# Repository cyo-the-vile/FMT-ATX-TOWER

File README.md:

# FMT-ATX-TOWER
A modification to revive a dead FM Towns tower model

[https://townsworld.com/2021/05/08/fm-towns-tower-power-supply-assembly-guide/](https://web.archive.org/web/20230320093739/https://townsworld.com/2021/05/08/fm-towns-tower-power-supply-assembly-guide/)

Uses an Arduino PRO Micro to control power on and TownsOS power off functions just like the original power supply.

Some of the mounting holes might not be exact.  At a later time, I need to measure the holes again but I don't own an original PCB anymore.  It is safe to file and cut around the screw points on the outer edges.

To order a PCB, go to factory output folder and select the RAR file.

Works on the following models:

1F
2F
SF
SH
1H
2H
10F
20F
40H
80H
SF2
SH2
CX10
CX20
CX40
CX100

It WILL NOT WORK for the following models:

S1
S2
MODEL1
MODEL2

You will need the following parts:

1    PCN13-44S-2.54DS
1	 39-28-1243    or you can use 39-28-1203.    It is preferred to use 39-28-1243
1    Arduino Pro Micro and Micro USB cable.  You need to load the firmware for the Arduino Pro Micro
1    Some male 2.54mm pin headers.
1    Pico PSU rated at 90W or higher such as this one   https://www.mini-box.com/picoPSU-90     The prototype was tested with 160W but I have found 90W is fine.
		Pico PSU have been cloned and their performance might vary. I recommend using the authentic mini-box brand.
1    AC/DC Converter.  The board can physically fit the EPS-120-12 or the EPS-120S-12.  Basically, an ACDC Converter that outputs 12V in a 2x3 or 2x4 (those are inches) form factor is fine.

日本人にとって、機械翻訳です。 あなたが困難を持っている場合は、Twitterで私に連絡してください。@cyothevile

死んだFMタウンズタワーモデルを復活させるための修正

[https://townsworld.com/2021/05/08/fm-towns-tower-power-supply-assembly-guide/](https://web.archive.org/web/20230320093739/https://townsworld.com/2021/05/08/fm-towns-tower-power-supply-assembly-guide/)

Arduino PRO Microを使用して、元の電源と同様に電源オンとTownsOSの電源オフ機能を制御します。

取り付け穴の中には、正確でないものもあります。 後で、私は再び穴を測定する必要がありますが、私はもう元のPCBを所有していません。 外縁のネジ点の周りをヤスリで留めて切断しても安全です。

PCBを注文するには、工場出荷時の出力フォルダに移動し、RARファイルを選択します。

次のモデルで動作します。

1F
2F
SF
SH
1H
2H
10F
20F
40H
80H
SF2
SH2
CX10
CX20
CX40
CX100

次のモデルでは動作しません。

S1
S2 
モデル1 or Model 1
モデル2 or Model 2

次の部品が必要です。

次の部品が必要です。

1 PCN13-44S-2.54DS
1 39-28-1243 または 39-28-1203 を使用できます。   39-28-1243 を使用することをお勧めします。
1 ArduinoプロマイクロとマイクロUSBケーブル。 Arduinoプロマイクロのファームウェアをロードする必要があります
1 いくつかのオス2.54mmピンヘッダー。
1 Pico PSUは、このような90W以上で定格 https://www.mini-box.com/picoPSU-90 プロトタイプは160Wでテストされましたが、90Wは問題ありません。
		Pico PSUはクローン化されており、それらのパフォーマンスは異なる場合があります。私は本物のミニボックスブランドを使用することをお勧めします。
1 AC / DCコンバータ。 ボードはEPS-120-12またはEPS-120S-12に物理的にフィットすることができます。 基本的に、2x3または2x4(これらはインチ)のフォームファクタで12Vを出力するACDCコンバータは問題ありません。

******************************************************

Generation 1 Tower card 

 - Requires more testing.  Should be safe for testing.

Please follow precise instructions here:  [https://townsworld.com/2021/06/01/fm-towns-power-supply-generation-1/](https://web.archive.org/web/20230603034252/https://townsworld.com/2021/06/01/fm-towns-power-supply-generation-1/)

VMS-180C-12
VOF-180C-12
VMS-200C-12

These are the recommended ACDC converters to place on the card.  The Generation 1 Towers appear to use more power.  A 160W Pico is recommended until further testing is completed.

ジェネレーション1タワーカード

日本人の友達、困ったら連絡してください。 TWITTER@cyo.the.vile

- さらにテストが必要です。テストのために安全でなければなりません。

こちらの正確な指示に従ってください: [https://townsworld.com/2021/06/01/fm-towns-power-supply-generation-1/](https://web.archive.org/web/20230603034252/https://townsworld.com/2021/06/01/fm-towns-power-supply-generation-1/)

VMS-180C-12
VOF-180C-12
VMS-200C-12

これらは、カードに配置する推奨 ACDC コンバータです。第 1 世代のタワーは、より多くの電力を使用しているようです。 さらなるテストが完了するまでは、160W Pico をお勧めします。

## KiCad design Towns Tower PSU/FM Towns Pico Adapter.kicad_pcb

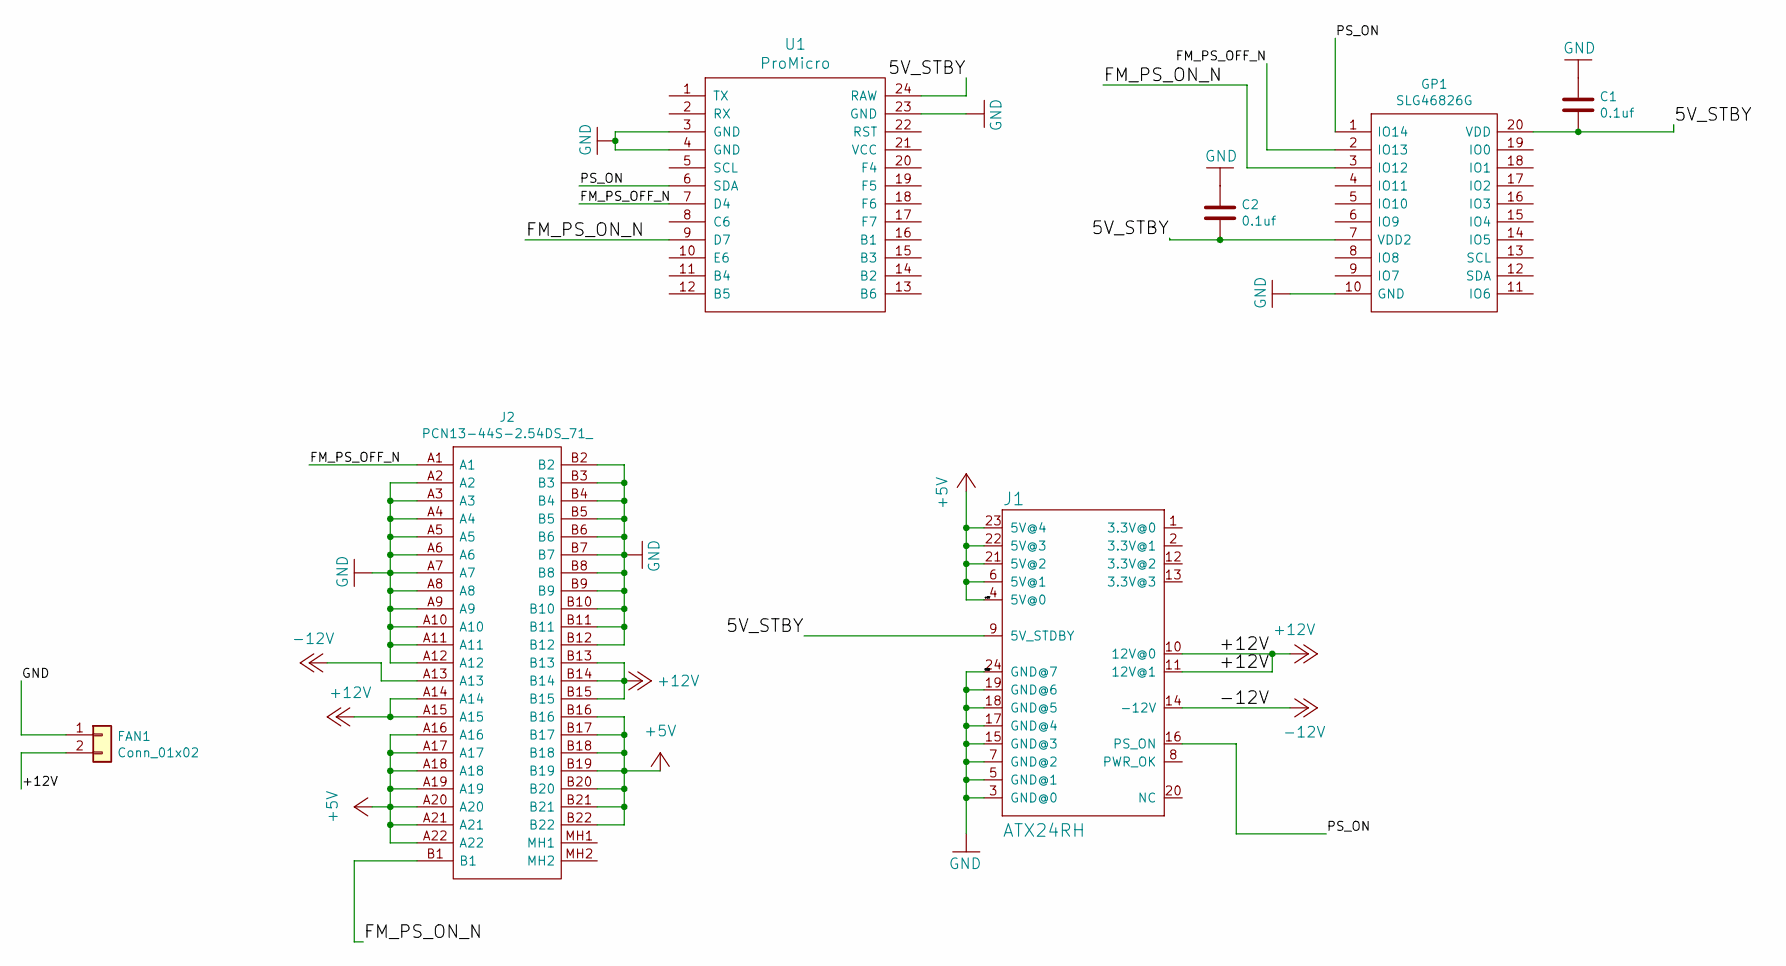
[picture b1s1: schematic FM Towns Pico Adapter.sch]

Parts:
C1, C2: 0.1uf; C_1206_3216Metric
FAN1: Conn_01x02; PinHeader_1x02_P2.54mm_Vertical
GP1: SLG46826G; SOP65P640X120-20N; Manufacturer_Part_Number SLG46826G; Mouser Part Number 724-SLG46826G
J1: ATX24RH; ATX24_RIGHT_ANGLE
J2: PCN13-44S-2.54DS_71_; PCN1344S254DS71; Manufacturer_Part_Number PCN13-44S-2.54DS(71); Mouser Part Number 798-PCN1344S254DS71
U1: ProMicro

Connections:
+5V: J1.4 (5V@0), J1.6 (5V@1), J1.21 (5V@2), J1.22 (5V@3), J1.23 (5V@4), J2.A16, J2.A17, J2.A18, J2.A19, J2.A20, J2.A21, J2.A22, J2.B16, J2.B17, J2.B18, J2.B19, J2.B20, J2.B21, J2.B22
+12V: FAN1.2, J1.10 (12V@0), J1.11 (12V@1), J2.A14, J2.A15, J2.B13, J2.B14, J2.B15
-12V: J1.14 (-12V), J2.A13
/5V_STBY: C1.2, C2.2, GP1.7 (VDD2), GP1.20 (VDD), J1.9 (5V_STDBY), U1.24 (RAW)
/FM_PS_OFF_N: GP1.2 (IO13), J2.A1, U1.7 (D4)
/FM_PS_ON_N: GP1.3 (IO12), J2.B1, U1.9 (D7)
/PS_ON: GP1.1 (IO14), J1.16 (PS_ON), U1.6 (SDA)
GND: C1.1, C2.1, FAN1.1, GP1.10 (GND), J1.3 (GND@0), J1.5 (GND@1), J1.7 (GND@2), J1.15 (GND@3), J1.17 (GND@4), J1.18 (GND@5), J1.19 (GND@6), J1.24 (GND@7), J2.A2, J2.A3, J2.A4, J2.A5, J2.A6, J2.A7, J2.A8, J2.A9, J2.A10, J2.A11, J2.A12, J2.B2, J2.B3, J2.B4, J2.B5, J2.B6, J2.B7, J2.B8, J2.B9, J2.B10, J2.B11, J2.B12, U1.3 (GND), U1.4 (GND), U1.23 (GND)

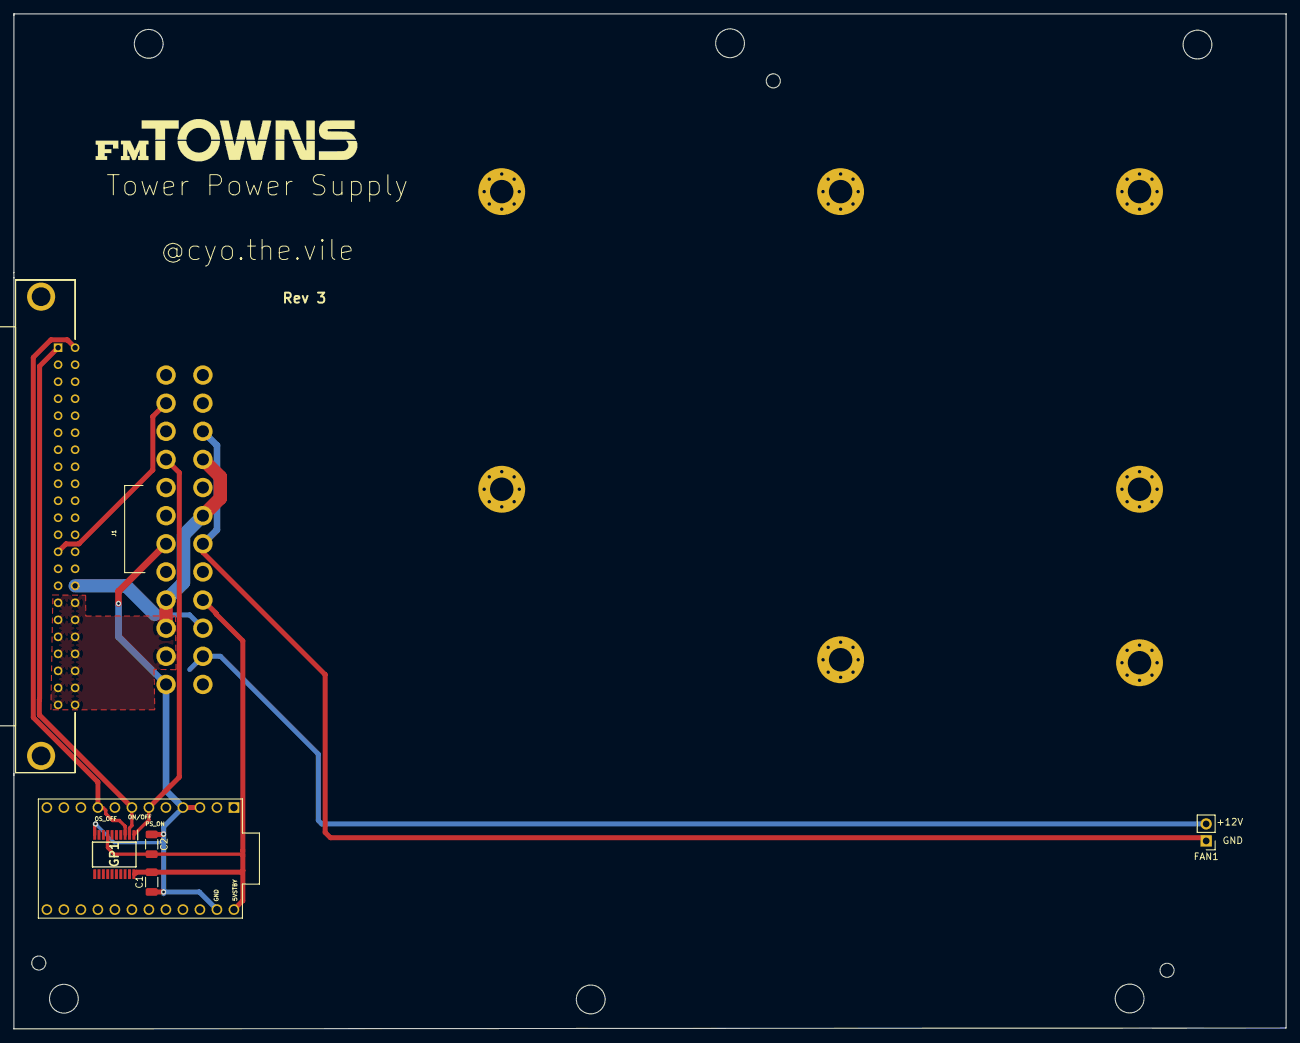
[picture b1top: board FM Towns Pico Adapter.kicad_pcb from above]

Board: 2 copper layers, 190.0 x 151.6 mm, 14 parts (0 on the bottom side), 8 nets.

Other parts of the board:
PAD1, PAD1#2, PAD1#3, PAD1#4, PAD2, PAD3, PAD4: MountingHole_3.5mm_Pad_Via

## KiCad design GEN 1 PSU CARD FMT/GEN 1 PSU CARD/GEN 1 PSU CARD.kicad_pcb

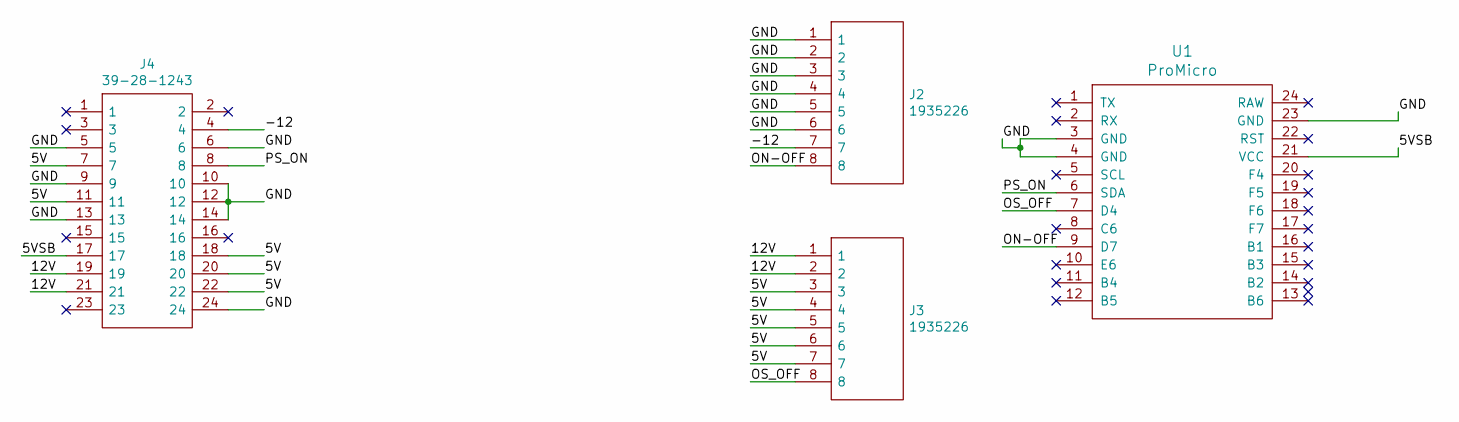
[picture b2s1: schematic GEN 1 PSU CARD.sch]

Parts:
J2, J3: 1935226; TerminalBlock_Phoenix_PT-1,5-8-3.5-H_1x08_P3.50mm_Horizontal; Manufacturer_Part_Number 1935226; Mouser Part Number 651-1935226
J4: 39-28-1243; SHDR24W125P550X420_2X12_5160X960X1310P; Manufacturer_Part_Number 39-28-1243; Mouser Part Number 538-39-28-1243
U1: ProMicro

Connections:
/5V: J3.3, J3.4, J3.5, J3.6, J3.7, J4.7, J4.11, J4.18, J4.20, J4.22
/5VSB: J4.17, U1.21 (VCC)
/12V: J3.1, J3.2, J4.19, J4.21
/-12: J2.7, J4.4
/GND: J2.1, J2.2, J2.3, J2.4, J2.5, J2.6, J4.5, J4.6, J4.9, J4.10, J4.12, J4.13, J4.14, J4.24, U1.3 (GND), U1.4 (GND), U1.23 (GND)
/ON-OFF: J2.8, U1.9 (D7)
/OS_OFF: J3.8, U1.7 (D4)
/PS_ON: J4.8, U1.6 (SDA)

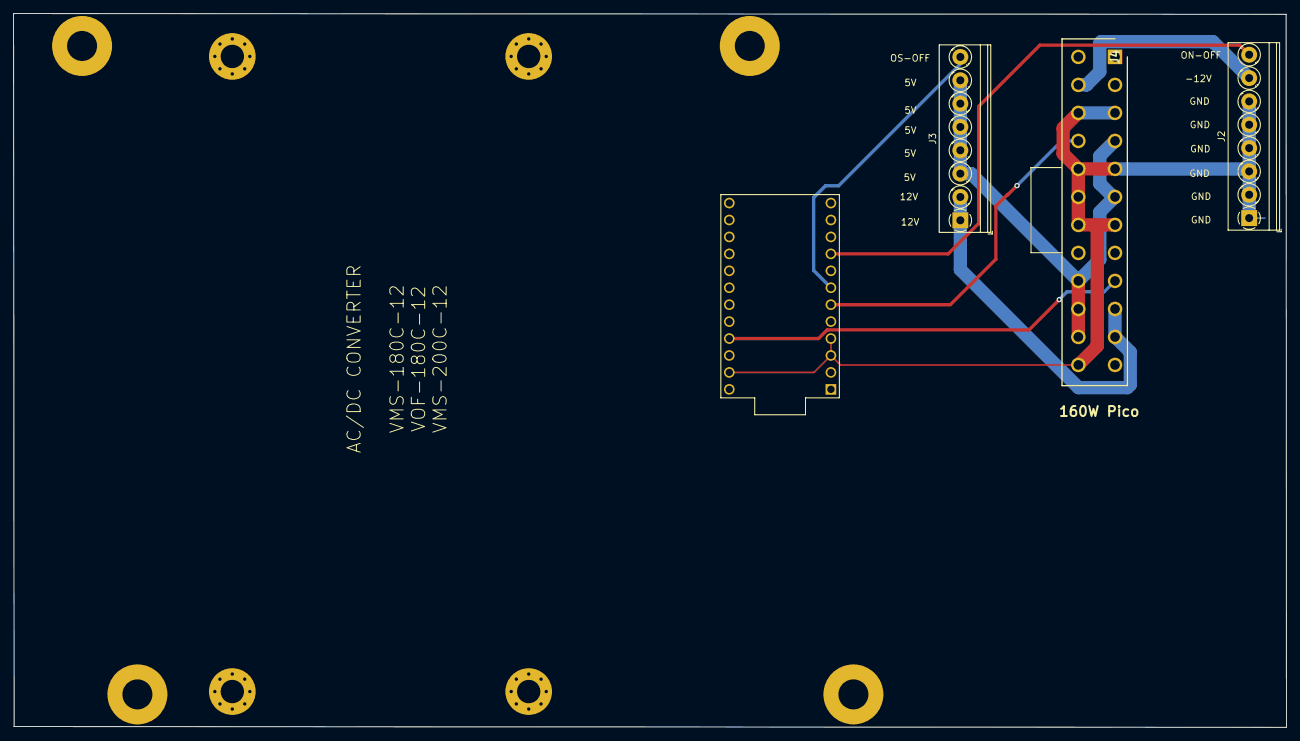
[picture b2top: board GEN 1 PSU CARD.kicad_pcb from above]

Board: 2 copper layers, 190.9 x 107.1 mm, 4 parts (0 on the bottom side), 8 nets.

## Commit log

2021-07-02 Update README.md
    Japanese support
2021-07-06 GEN1 card
    Generation 1 card changes
2021-07-06 Update README.md
    Added Gen 1 support
2022-08-08 Rev2
    -Remeasured and added support holes for the ACDC converters in 2x4 form factor
    -Verification of original mounting holes is still required
2022-08-08 Gen 1 Card update
    -Revised Gen1 card and added high power ACDC converter footprint and repositioned components so it's two layer.
2022-08-08 Update
    Updated Rev2
    Now 2 Layer card
2023-06-15 TownsPSU Rev3
    -SLG62686 footprint added. Will add configuration file once verified on hardware although I don't see anyone using them.
    -Moved fan connector since someone complained
